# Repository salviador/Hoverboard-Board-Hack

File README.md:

- **"Hoverboard-Board-Hack/motor hack/"** hoverboard pcb STM32F103
 - **Optional, "STM32_BLE - JOY"** pcb, schematic, code for bluetooth interface
 - **wheel/wheel** APP Android, code in xamarin

> Written w

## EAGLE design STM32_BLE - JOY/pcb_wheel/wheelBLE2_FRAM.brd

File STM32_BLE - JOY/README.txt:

Use: pcb_wheel\wheelBLE.brd
Firmware: STM32L0_BLE - JOY

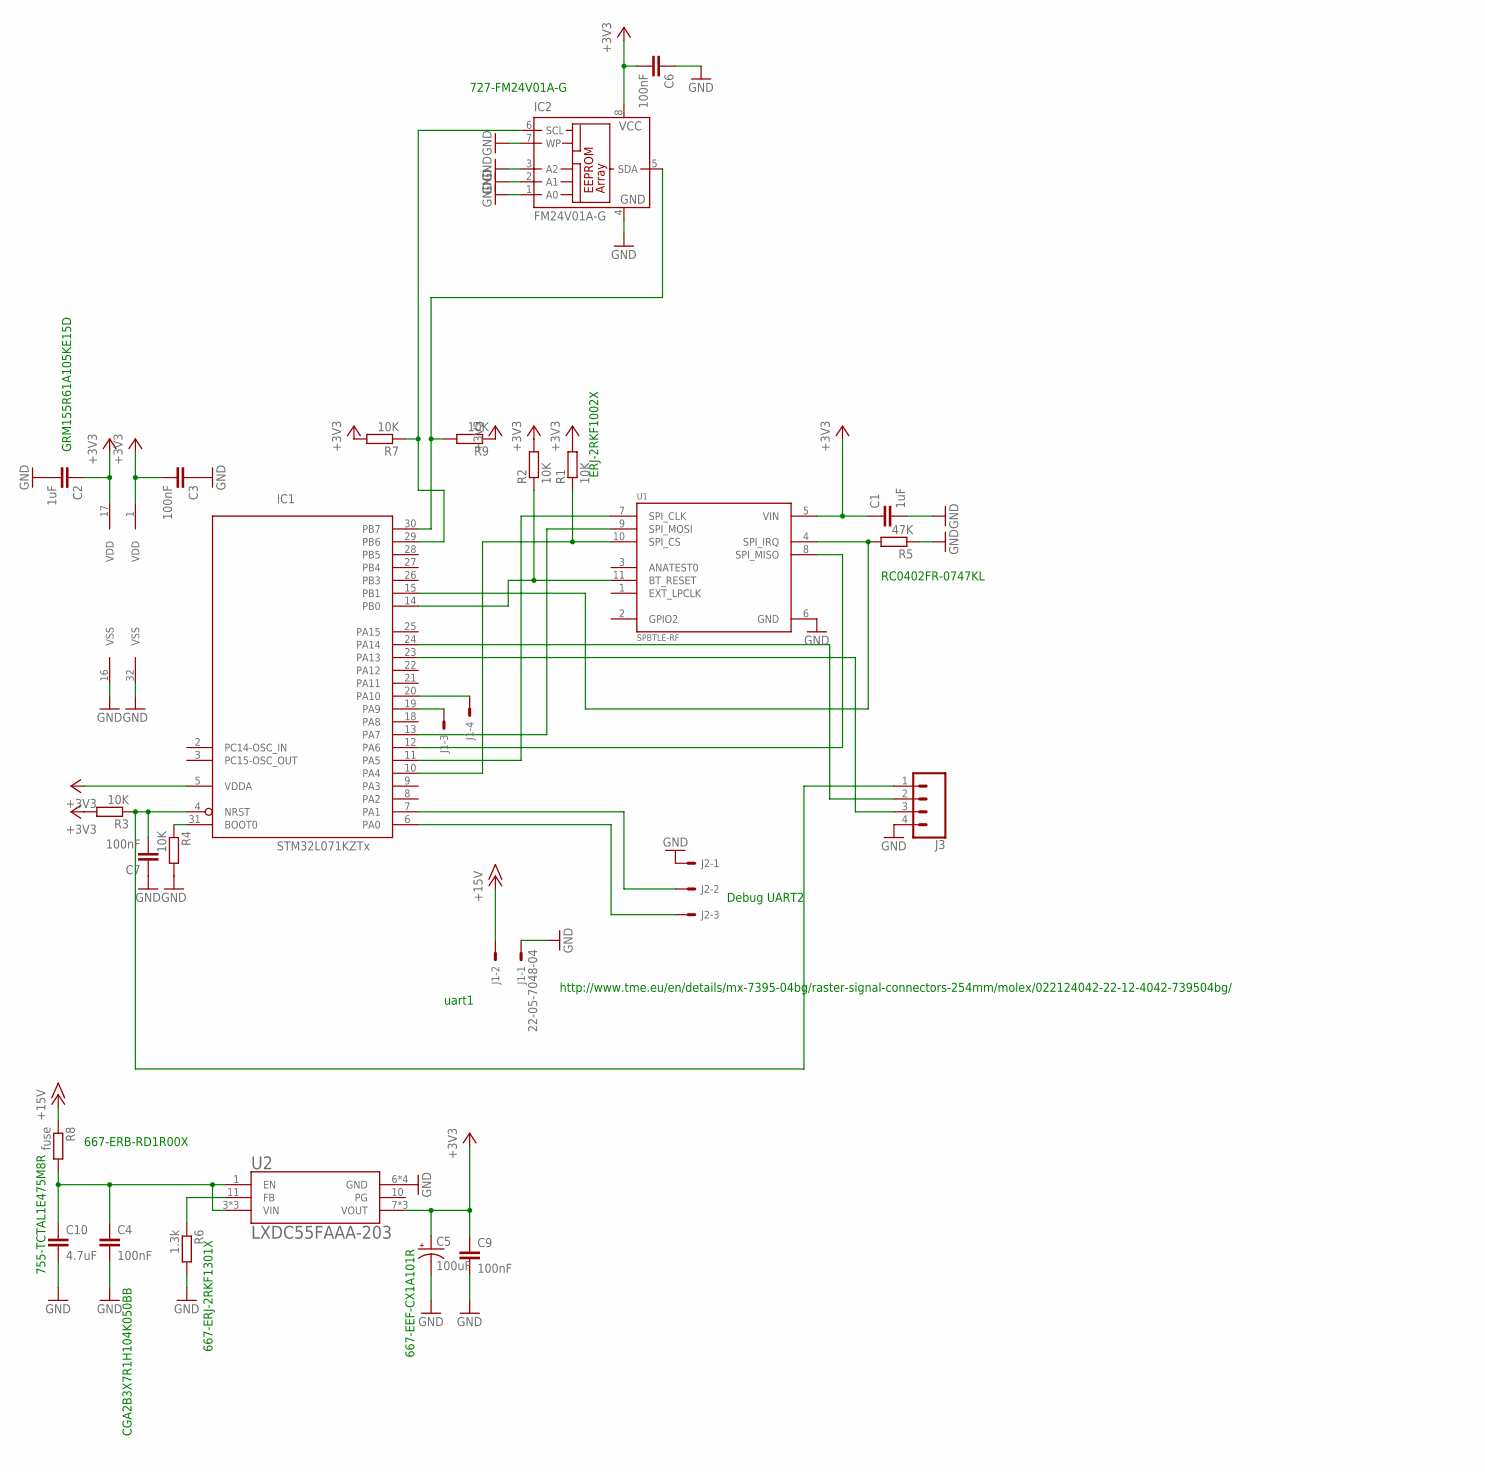
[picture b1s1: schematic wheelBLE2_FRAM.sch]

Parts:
C1, C2: 1uF; C0402
C3, C4, C6, C7, C9: 100nF; C0402
C5: 100uF; EIA7343
C10: 4.7uF; 1206
IC1: STM32L071KZTx; LQFP32
IC2: FM24V01A-G; SO-08M
J1: 22-05-7048-04; 7395-04
J2: 22-05-7038-03; 7395-03
J3: CONN_04; 1X04
R1, R2, R3, R4, R7, R9: 10K; R0402
R5: 47K; R0402
R6: 1.3k; R0402
R8: fuse; R0402
U1: SPBTLE-RF; XCVR_SPBTLE-RF
U2: LXDC55FAAA-203; CONV_LXDC55FAAA-203

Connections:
+3V3: C1.1, C2.1, C3.2, C5.A (+), C6.2, C9.1, IC1.1 (VDD), IC1.5 (VDDA), IC1.17 (VDD), IC2.8 (VCC), R1.2, R2.2, R3.2, R7.2, R9.1, U1.5 (VIN), U2.7 (VOUT), U2.8 (VOUT), U2.9 (VOUT)
+15V: J1.2, R8.1
GND: C1.2, C2.2, C3.1, C4.2, C5.C (-), C6.1, C7.1, C9.2, C10.2, IC1.16 (VSS), IC1.32 (VSS), IC2.1 (A0), IC2.2 (A1), IC2.3 (A2), IC2.4 (GND), IC2.7 (WP), J1.1, J2.1, J3.4, R4.2, R5.1, R6.2, U1.6 (GND), U2.6 (GND), U2.12 (GND), U2.13 (GND), U2.14 (GND)
unnamed: IC1.10 (PA4), R1.1, U1.10 (SPI_CS)
unnamed: IC1.14 (PB0), R2.1, U1.11 (BT_RESET)
unnamed: C7.2, IC1.4 (NRST), J3.1, R3.1
unnamed: IC1.31 (BOOT0), R4.1
unnamed: IC1.11 (PA5), U1.7 (SPI_CLK)
unnamed: IC1.12 (PA6), U1.8 (SPI_MISO)
unnamed: IC1.13 (PA7), U1.9 (SPI_MOSI)
unnamed: IC1.6 (PA0), J2.3
unnamed: IC1.19 (PA9), J1.3
unnamed: IC1.20 (PA10), J1.4
unnamed: IC1.15 (PB1), R5.2, U1.4 (SPI_IRQ)
unnamed: IC1.7 (PA1), J2.2
unnamed: R6.1, U2.11 (FB)
unnamed: C4.1, C10.1, R8.2, U2.1 (EN), U2.3 (VIN), U2.4 (VIN), U2.5 (VIN)
unnamed: IC1.23 (PA13), J3.3
unnamed: IC1.24 (PA14), J3.2
unnamed: IC1.30 (PB7), IC2.5 (SDA), R9.2
unnamed: IC1.29 (PB6), IC2.6 (SCL), R7.1

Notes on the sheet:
http://www.tme.eu/en/details/mx-7395-04bg/raster-signal-connectors-254mm/molex/022124042-22-12-4042-739504bg/
Debug UART2
uart1
667-ERB-RD1R00X
755-TCTAL1E475M8R
667-EEF-CX1A101R
CGA2B3X7R1H104K050BB
GRM155R61A105KE15D
667-ERJ-2RKF1301X
ERJ-2RKF1002X
RC0402FR-0747KL
727-FM24V01A-G

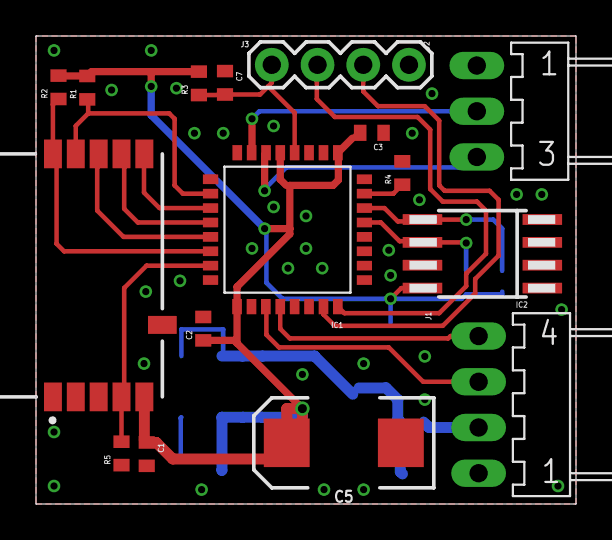
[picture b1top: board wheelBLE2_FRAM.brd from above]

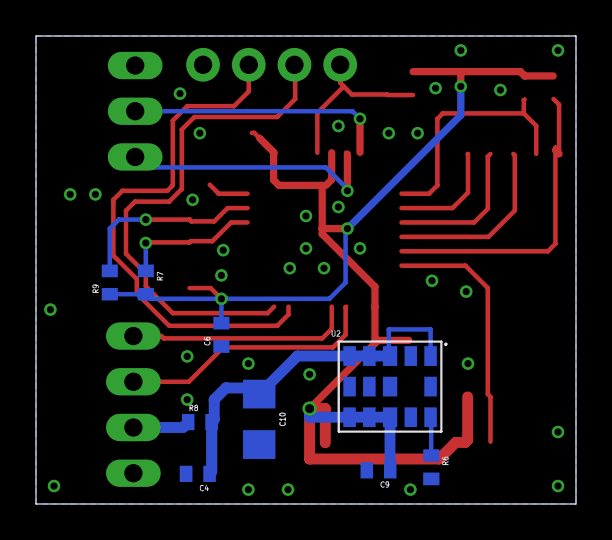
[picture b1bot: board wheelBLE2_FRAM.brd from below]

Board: 2 copper layers, 30.0 x 26.0 mm, 25 parts (9 on the bottom side), 21 nets.

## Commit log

2017-02-22 :lollipop: Added .gitattributes & .gitignore files
2017-02-22 Hoverboard Board Hack
2017-02-22 firmware
2017-02-25 update2
2017-02-28 update3
2017-03-01 Arduino 101 Update
    use with Blynk
2017-03-07 update board viwe
2017-03-21 update android
2017-03-24 update 4
2017-03-24 bug arduino
2017-03-24 bug motor
2017-03-31 update android pairing
2017-04-01 stm32 ble
2017-04-02 pcb update
2017-04-03 icon
2017-04-03 color
2017-04-03 disconnessione
2017-04-08 bux fix
2017-04-08 bugfix ble
2017-04-10 update sram
2017-06-03 BLE update
2017-06-03 motorUpdate
2017-06-03 update motor
2017-06-04 Update version
2017-06-04 update version ble
2017-08-12 image

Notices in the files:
parts and their libraries:
SparkFun-Capacitors: Licensing: Creative Commons ShareAlike 4.0 International - https://creativecommons.org/licenses/by-sa/4.0
